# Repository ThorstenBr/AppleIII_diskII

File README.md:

# Apple III to disk II / FloppyEmu Adapter
This project decribes how to build an adapter connecting an Apple III to a [FloppyEmu from Big Mess of Wires](https://www.bigmessowires.com/floppy-emu/) - an SD-card based disk drive emulator.
Alternatively, the adapter can also be used to connect the Apple III to an original Apple **Disk II** drive (yes, Disk II, not Disk III).
The adapter works with either the internal or external floppy port of the Apple III.

As a bonus I also added a design file for a 3D-printed slim enclosure:

## License
This project is released under the "Creative Commons Attribution 4.0 International Public License". See [LICENSE](LICENSE).

## Description
It doesn't take much to connect a FloppyEmu to an Apple III. The disk drive interface of the Apple III is very similar to the Apple II - with most signals being completely identical. The Apple III, however, has a few extra signals and features, hence it uses a wider 26pin connector, instead of the 20pin connector of the Apple II. Most extra pins are not required for normal operation.

A few people have made the connection between Apple III and FloppyEmu/DiskII with a simple ribbon cable: using a 26pin IDC connector at one end, and a 20pin IDC connector (stripping the top 6 wires) at the other end. That did mostly work (if you don't mess up, reverse the connectors or strip wires from the wrong side, that is...). You can find more on this in [Steve's (BMOW) blog post](https://www.bigmessowires.com/2017/01/25/floppy-emu-on-the-apple-iii/).

**However**, such a simple 26pin to 20pin cable is not to be recommended - and it will not always work. For proper operation, one of the additional signals also has to be considered (see the "errata" section below, if you are interested in the details).

This adapter uses a cheap logic IC (74LS32) to properly decode the Apple /// drive enable signals and provide a signal to FloppyEmu or disk II. When connected to a FloppyEmu, the adapter also supports its "dual drive emulation" feature, where it emulates two separate disk drives.

The adapter can be connected to the Apple III disk port (internal or external port) and provides a standard 20pin connector, which can be used directly with the original FloppyEmu/Disk II cables.

### Using the Apple III external floppy port
You can connect the adapter to the external floppy port at the rear of your Apple III.

* **Disk II**: When using the external floppy port, the connected disk II drive acts as the system's "drive #2" (".D2", which confusingly is sometimes also refered to as "**external** drive #1").
* **FloppyEmu**: When connecting a FloppyEmu, you can enable its dual drive support. In this case your FloppyEmu will emulate the system "drive #2" and "drive #3" (".D2" and ".D3" - which are sometimes also called "**external** drives #1 and #2"). So, including the internal drive, you then have three floppy drives connected to your Apple III.

### Using the Apple III internal floppy port
The internal port connects the boot drive (system drive #1).
You can simply unplug the installed ribbon cable from the internal drive and plug it to the adapter's Apple III port.
No extra cable is required.

When using the internal Apple III floppy port, the connected drive acts as drive #1 (".D1", boot drive).
The internal port does not support the signals for the external drives, however.
So, unfortunately you cannot make use of FloppyEmu's dual drive support to also emulate drive #2, when using the internal connector.

If you connect a new cable to the mainboard: the internal port is located on the mainboard right next to the external port:

## Parts List
Parts list for the completed PCB:
* 1x 20pin box header
* 1x 26pin box header
* 1x 14pin DIP socket (recommended)
* 1x IC SN74LS32 "OR-Gate" (74HCT32 also works but requires the optional 3K3 resistors)
* 1x 470 Ohm resistor
* 2x 3.3K Ohm resistors (optional/recommended)
* PCB (see Gerber files below)

<!--

-->

Additionally, if you wanted to use Apple III's external floppy port, you may need a short 26pin ribbon cable with appropriate IDC sockets.
* 2x 26-pin IDC socket (with strain relief)
* 1x 26pin ribbon cable (a few inches/centimers are enough)

A very short ribbon cable will be enough for the external port (since your disk II/floppyEmu already comes with a long ribbon cable). Note, if you have any wider ribbon cables, you can easily reduce them to the appropriate wire count (so you would not need to shop an entire roll of new 26-write ribbon cable).

If you make your own ribbon cable: **MAKE SURE THE IDC SOCKETS ARE ORIENTED CONSISTENTLY!** Do not flip or reverse the orientation of the connectors (place them on the same side of the ribbon cable and with the notch facing the same direction).

For the internal floppy port you can reuse the existing floppy cable of your Apple III (unplug the internal floppy and plug the cable into the adapter instead).

I ordered parts from my usual German electronics online shop for less than a buck. Add a few bucks if you need a new ribbon cable ([Shopping List at Reichelt.de](https://www.reichelt.de/my/1980987?LANGUAGE=EN)).
I created a public shopping list containing all the parts. All parts are extremely common and will be available for a long time.

## Gerber Files, Ordering a PCB
If you wished to directly order a PCB (PCBWay, JLCPCB etc) you could use the latest Gerber files from the [Gerber](Gerber/) directory. Just upload the ZIP file to your preferred PCB manufacturer and order the PCB. My PCBs were manufactured by JLCPCB (using the cheapest options, I got mine already after about 1.5 weeks for a few bucks/Euros).

## Soldering
Soldering is straight forward. Only simple through-hole components are used. All part numbers and component values are marked directly on the PCB.

**DOUBLE-CHECK THE PROPER ORIENTATION OF THE BOX HEADERS!**  
The notch for the box headers are clearly marked on the PCB.
Incorrect orientation of the box headers for the Apple III or FloppyEmu port will damage or destroy your Apple III and FloppyEmu/disk II drive - or both...

The capacitor (C1) was added on the PCB as a backup. It is not required (leave the slot unused).

### Soldering Options
There are three solder jumpers on the bottom side of the adapter:

* **JP1**: connects the "drive 2" signal to the 20-pin connector. This signal enables dual drive support of FloppyEmu. This signal cannot be used when connecting an original Apple disk II drive, though. Setting this jumper will not damage anything when a disk II drive was connected, since there is also a resistor protecting the pin. But it adds unnecessary load. So, it's recommended to only close JP1 when you connect a FloppyEmu (and intend to use the dual drive support). Otherwise leave this jumper open.
* **JP2, JP3**: These jumpers connect -12V and +12V to the 20pin floppy header. These voltage supplies are required for the Apple disk II drive. But they are not required by FloppyEmu. It's recommended to leave these jumpers open if you intend to only connect a FloppyEmu. But they have to be closed when you wanted to connect an original disk II drive.

## Installation
Make sure the Apple III is switched off. **Do not connect the adapter, the Disk II, or Floppy Emu while your machine is powered!**

* Connect the adapter to the external floppy port at the rear of your Apple III (26pin ribbon cable required). Alternatively, connect it to the internal floppy port: pull the 26pin ribbon cable from the internal disk drive and plug it into the adapter.
* Finally connect the FloppyEmu's ribbon cable to the adapter. The FloppyEmu cable has a keyed connector (with a notch), so it should only fit in correct orientation.

* Alternatively, when you use the adapter to connect a Disk II drive, be extra careful: the Disk II connectors do not have a notch preventing incorrect orientation. You can easily plug them reversed, which will damage the drive and/or interface card. Pin 1 is marked with a little triangle on the PCB, on the 3D-printed enclosure - and also on the disk II connector.

### Configuring the System for Three Drives

If you connect the FloppyEmu to the external connector, your system has three drives (the internal disk drive, and two external drives emulated by FloppyEmu).
However, with Apple's "SOS" operating system it is necessary to configure the system to make the third drive work (if your system was previously configured for two drives only).

Here are some hints on how to configure the Apple III:

* Use the "system utilities" disk.
* Enter the "System Configuration Program (SCP)".
* Select "Read a Driver File" to read ".D1/sos.driver" from your boot disk.
* Select "Change System Parameters".
* Set "Number of Disk III Drives" to 3 (or 4...).
* Select "Generate New System" and write the new configuration to ".D1/sos.driver" of your boot disk.

Yes, changing the configuration of the Apple III SOS is a bit inconvenient. :)
And make sure you have a backup of your boot disk, before you reconfigure anything...

## Errata / Technical Background ##
As described above, a number of people have made adapters by simply stripping away the 6 additional signals from the wider Apple III connector, and connect the 20 identical signals to a FloppyEmu/Disk II (in fact: the first version of the adapter in this project also followed this basic approach).

This will mostly work - when each drive is used individually. However, the Apple /// has a feature, which Apple IIs do not have: the Apple /// disk drive logic is able to keep the motor of the internal disk drive **and** one external disk drive spinning concurrently. This significantly speeds up the performance when copying data between internal and external disks - or when quickly reading files from both drives. The computer is no longer delayed by waiting for drive to reach their target rotation speed, when the drives keep spinning concurrently.

This feature is used on the Apple ///, for example, when using the "volume copy" feature of "SOS system utilties". While copying an entire disk, it keeps both drives spinning, while reading data from one disk and immediately writing it to the other. Disk copying is therefore much faster on the Apple III than on an Apple II (where the computer again and again needs to briefly wait while the two drives spin up and down).

This feature is implemented by Apple /// by keeping the *enable signals* for the internal and one of the external drives both enabled. These signals are at the same pin location as the respective signals of Apple II drives. However, on the Apple II it is forbidden for more than one drive to be enabled concurrently, since this would result in a conflict on the other shared communication signals. On the Apple II these signals meant "*enable motor **and** communication*". The Apple ///, however, has an additional signal on its 26pin port, which selects between internal and external communication. The disk enable signal on the Apple III only means "*enable motor*" - and therefore allows more than one drive to be enabled (spinning) at the same time. Still, communication always takes place with one drive only, when *additionally* an extra signal on the 26pin connector selects the internal port (or external port, respectively).

This adapter uses a simple 74LS32 logic IC (OR-gate), which properly considers all Apple III disk enable signals - and provides the correct signal to FloppyEmu (or disk II).

If you use CMOS logic devices (74HCT32) then the two pull-up resistors are required (they are recommended anyway).

## Schematics and KiCad Project
The [KiCad](KiCad/) folder contains the schematics and PCB project files, if you wished to adapt the design.

## Bonus: 3D-printed enclosure
As a bonus, I also added a design for a 3D-printed enclosure.
It's a neat and slim box which completely covers the PCB - eliminating any risk of creating short-circuits (remember the bottom side of the PCB has +/-12V and +5V voltage pins - so it's a good idea to cover them).
You'll find the 3D file (.stl) in the [/3DPrint](3DPrint/) folder.

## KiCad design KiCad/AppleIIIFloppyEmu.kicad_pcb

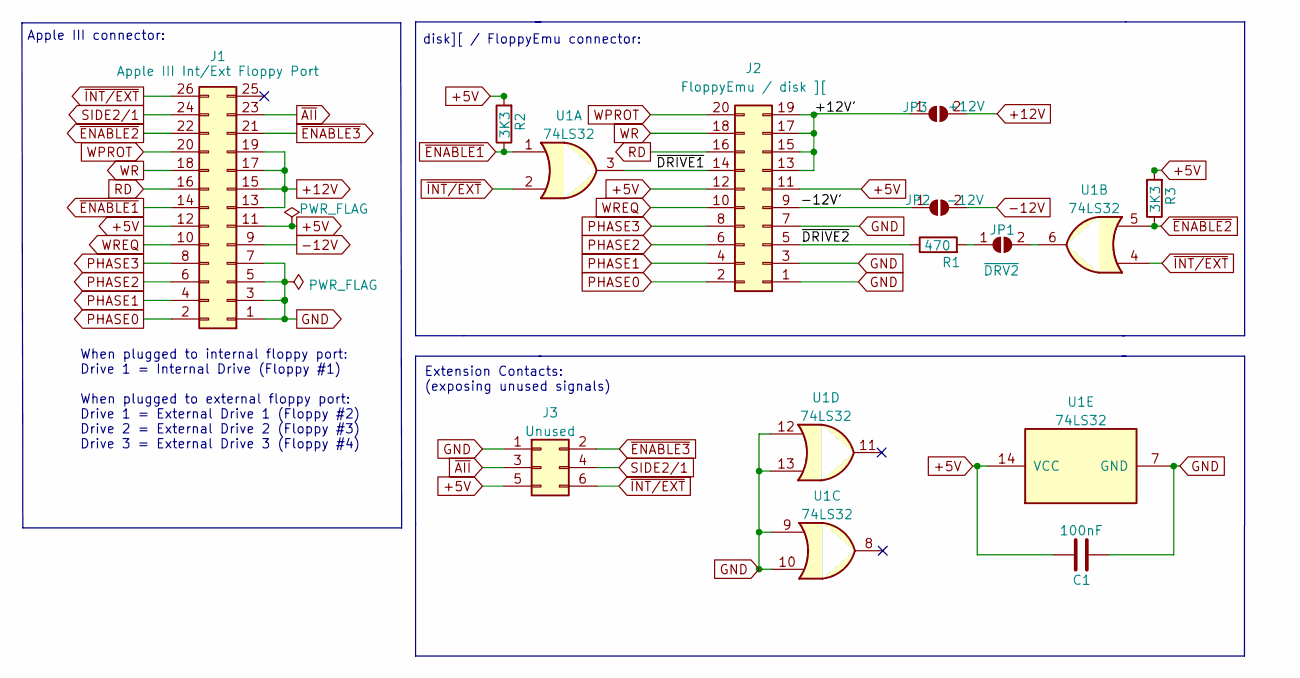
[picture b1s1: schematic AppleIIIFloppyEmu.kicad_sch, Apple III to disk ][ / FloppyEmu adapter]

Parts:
C1: 100nF; C_Disc_D4.7mm_W2.5mm_P5.00mm
J1: Apple III Int/Ext Floppy Port; IDC-Header_2x13_P2.54mm_Vertical
J2: FloppyEmu / disk ][; IDC-Header_2x10_P2.54mm_Vertical
J3: Unused; PinHeader_2x03_P2.54mm_Vertical
JP1: ~{DRV2}; SolderJumper-2_P1.3mm_Open_RoundedPad1.0x1.5mm
JP2: -12V; SolderJumper-2_P1.3mm_Open_RoundedPad1.0x1.5mm
JP3: +12V; SolderJumper-2_P1.3mm_Open_RoundedPad1.0x1.5mm
R1: 470; R_Axial_DIN0207_L6.3mm_D2.5mm_P10.16mm_Horizontal
R2, R3: 3K3; R_Axial_DIN0207_L6.3mm_D2.5mm_P10.16mm_Horizontal
U1: 74LS32; DIP-14_W7.62mm_Socket_LongPads

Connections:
+5V: C1.1, J1.11, J1.12, J2.11, J2.12, J3.5, R2.2, R3.2, U1.14 (VCC)
+12V: J1.13, J1.15, J1.17, J1.19, JP3.2 (B)
-12V: J1.9, JP2.2 (B)
/+12V': J2.13, J2.15, J2.17, J2.19, JP3.1 (A)
/-12V': J2.9, JP2.1 (A)
/~DRIVE1: J2.14, U1.3
/~DRIVE2: J2.5, R1.1
GND: C1.2, J1.1, J1.3, J1.5, J1.7, J2.1, J2.3, J2.7, J3.1, U1.7 (GND), U1.9, U1.10, U1.12, U1.13
unnamed: JP1.1 (A), R1.2
unnamed: JP1.2 (B), U1.6
PHASE0: J1.2, J2.2
PHASE1: J1.4, J2.4
PHASE2: J1.6, J2.6
PHASE3: J1.8, J2.8
RD: J1.16, J2.16
SIDE2/1: J1.24, J3.4
WPROT: J1.20, J2.20
WR: J1.18, J2.18
WREQ: J1.10, J2.10
~AII: J1.23, J3.3
~ENABLE1: J1.14, R2.1, U1.1
~ENABLE2: J1.22, R3.1, U1.5
~ENABLE3: J1.21, J3.2
~INT/EXT: J1.26, J3.6, U1.2, U1.4

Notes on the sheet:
Extension Contacts: (exposing unused signals)
When plugged to internal floppy port: Drive 1 = Internal Drive (Floppy #1) When plugged to external floppy port: Drive 1 = External Drive 1 (Floppy #2) Drive 2 = External Drive 2 (Floppy #3) Drive 3 = External Drive 3 (Floppy #4)
Apple III connector:
disk][ / FloppyEmu connector:

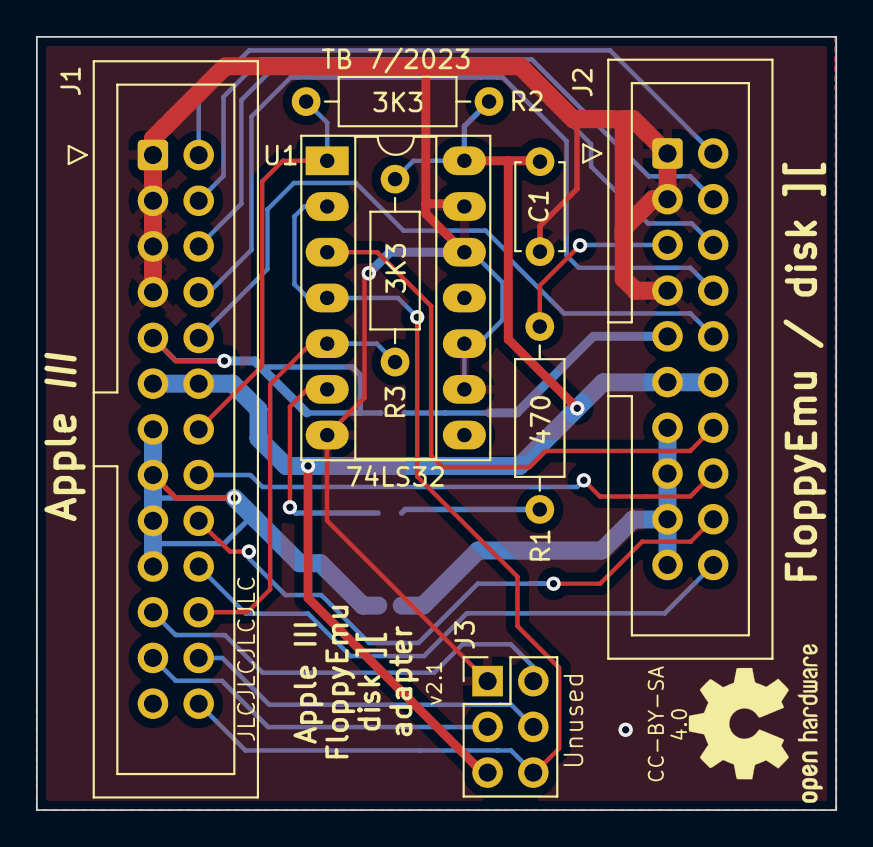
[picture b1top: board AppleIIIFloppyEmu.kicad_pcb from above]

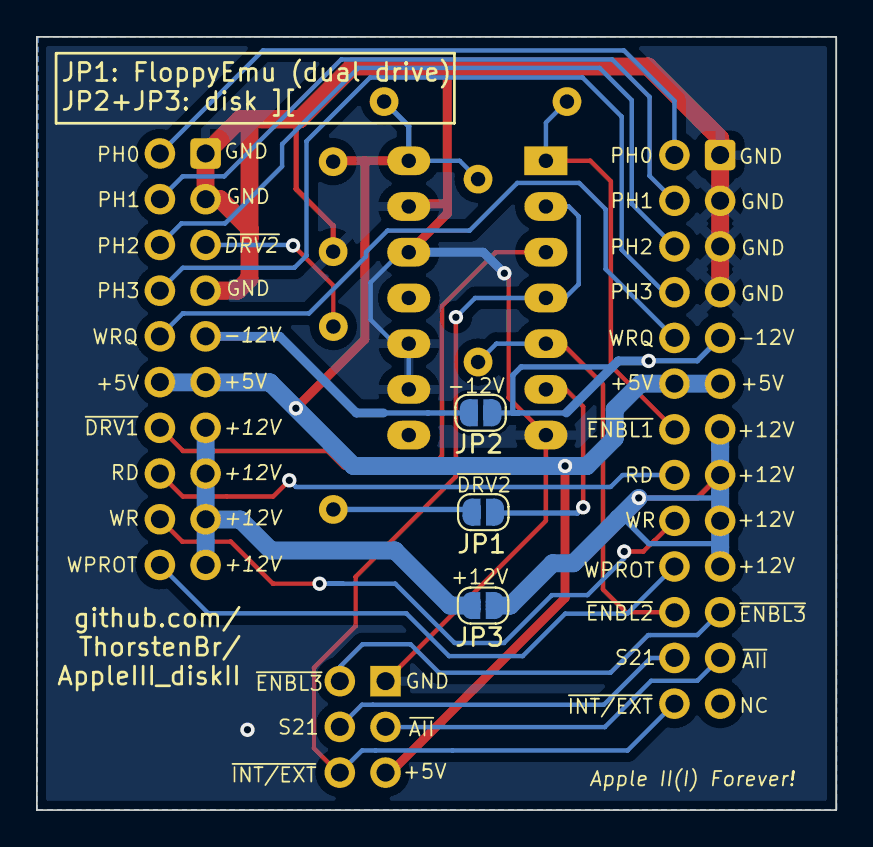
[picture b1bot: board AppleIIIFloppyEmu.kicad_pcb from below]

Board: 2 copper layers, 44.4 x 43.0 mm, 11 parts (3 on the bottom side), 24 nets.

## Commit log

2022-09-25 Initial revision: v1.0
2022-09-25 Updated README. Update to rev 1.1.
2022-10-22 Added photos of completed PCB
2022-10-23 Added description on how to configure the Apple III SOS for three drives
2022-10-23 Added design files for 3D-printed enclosure
2022-10-23 Dropped the v1.0 Gerber file.
2022-10-24 Added another photo of the 3D print.
2022-11-06 Updated to v2.0: properly handle Apple /// Disk logic when SOS keeps the internal and one external drive spinning concurrently, while alternating the access to both drives. SOS uses this feature when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
2022-11-06 Minor README updates.
2022-12-05 Updated with photo of latest PCB revision.
2022-12-07 Adapted 3D printed enclosure to latest PCB design.
2023-07-15 Added optional pull-ups to ENBL1+2 to allow use of 74HCT32 ICs. The pull-ups (R2+R3) are not strictly required for 74LS32 ICs (but recommended anyway). R3 may be soldered on the top side, before sold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

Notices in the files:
KiCad/AppleIIIFloppyEmu.kicad_pcb:
CC-BY-SA
